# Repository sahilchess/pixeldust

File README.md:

# Pixeldust 🌟

Pixeldust is a new (in development) YSWS @ Hack Club! Create your own PCB design using KiCad, write the firmware for it in Wokwi, then receive your PCBs in the mail!

The website is still under development (guides etc. have been created yet) But the home page of the site has been created

## What is Pixeldust?

This is a brand new (in development) YSWS where you design your own neopixel-based PCB trinket, and we'll ship it to you for free! Make sure to join #pixeldust in the slack so you dont miss out!!

### You ship...

- A PCB design for the board
- Working firmware to control the neopixels

### We ship...

- 1 fully assembled PCB
   - This will include your XIAO RP2040 as well as the neopixels

- 2 unassembled PCBs

## Requirements

- Your firmware must be working!!! We won't approve any without.
- It must be more complex than just a simple blinking LED
- Your PCB cannot exceed 100cm^2
- Your PCB must only use 2 layers

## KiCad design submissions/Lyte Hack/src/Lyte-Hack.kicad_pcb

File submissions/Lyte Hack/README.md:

---
name: "Reem Ahrabar"
slack_id: "U07TZLFLJFR"
github_handle: "@cloudTwelve"
tutorial: "https://pixeldust.hackclub.com/guidelines"
wokwi: "https://wokwi.com/projects/428996000515740673"
---

# Lyte Hack

Wokwi link: [https://wokwi.com/projects/428996000515740673](https://wokwi.com/projects/428996000515740673)

<!-- Uncomment the line below if you need a soldering iron -->
<!-- ⚠️ I would like to solder the pieces of the board myself, so I would need some solder (I have an iron, but lost my solder). Nevermind, disregard -->

### Description
This is my submission for Hack Club's Pixeldust YSWS, and it's for a light that goes beneath a water bottle to turn it into a lamp. It was inspired by a life hack I heard of when I was younger and loved watching life hack videos, which instructed the viewer to put their phone's flashlight beneath a bottle to turn it into a lamp. I thought it'd be great to make a PCB version of this (with, inshaAllah/God willing, a 3D printed case + model for this later) since I had the opportunity.

### Concept Images

### Features
- 2 modes:
  -  White
  -  Color
    - Red
    - Orange
    - Yellow
    - Green
    - Turquoise
    - Blue
    - Indigo
    - Purple
    - Cotton candy (interspersed pale blue/pink)

### A simplified BOM table
(pls include rough pricing of any extra components you're using)

| Comment           | Footprint                                      | Quantity | LCSC     | Cost   |
|-------------------|------------------------------------------------|----------|----------|--------|
| 100uF             | C_1206_3216Metric_Pad1.33x1.80mm_HandSolder    | 1        | C15008   | 0.0682$|
| 4.7nF             | C_0402_1005Metric_Pad0.74x0.62mm_HandSolder    | 3        | C1538    | 0.0011$|
| SK6812MINI        | LED_SK6812MINI_PLCC4_3.5x3.5mm_P1.75mm         | 10       |          |
| XIAO-RP2040-DIP   | XIAO-RP2040-DIP                                | 1        |          |
| B3S-1000          | SW_SPST_B3S-1000                               | 2        | C2733655 | 0.2327$ each for 5|

### Planning/Making
I started this when the event was already over, and I had been thinking of chilling with hw late at night using the lamp life hack, realizing it could be translated to a PCB + 3D printed design. Since I had already done Hackpad V2 (still waiting on a PR approval though) for the macropad, I had a small but encouraging history with PCBs. I was ready to try again and make something fun, so I tried speedrunning this.

#### The Schematic
This went quickly. Following the guide given on the pixeldust website, I breezed through. The only new thing was the concept of decoupling capacitors (I should really learn electrical engineering...). I had to change a footprint when filling out the README, since the button I initially used (B3S-1100) was out of stock.

#### The PCB
This was also simple, I just listened to YouTube lectures and podcasts while I positioned and routed the items. The routing is pretty sloppy, in the future I'd probably watch a video on cleaner routing + good practices before doing this. Nevertheless, Hackpad gave me a good base, and the only issue I had was having to come back when small schematic issues cropped up (eg. changing the footprint for the button) and re-route/reposition items.

#### The Firmware
I had high aspirations that were partially fulfilled. Initially, I wanted 3 modes, static white, static color, and animated color, but I ended up throwing out the animated mode because of time. Some struggles I faced were:
- Finding the button library. Wokwi used MicroPython, not CircuitPython. I'd never used either, but I initially used the button library from CircuitPython.
- Getting the neopixel library to work. Same issue as above.
- Button timing. Often, the button would register multiple times on one click, and to fix it, I disabled the interrupt function, delayed 0.75s, and then enabled it again.

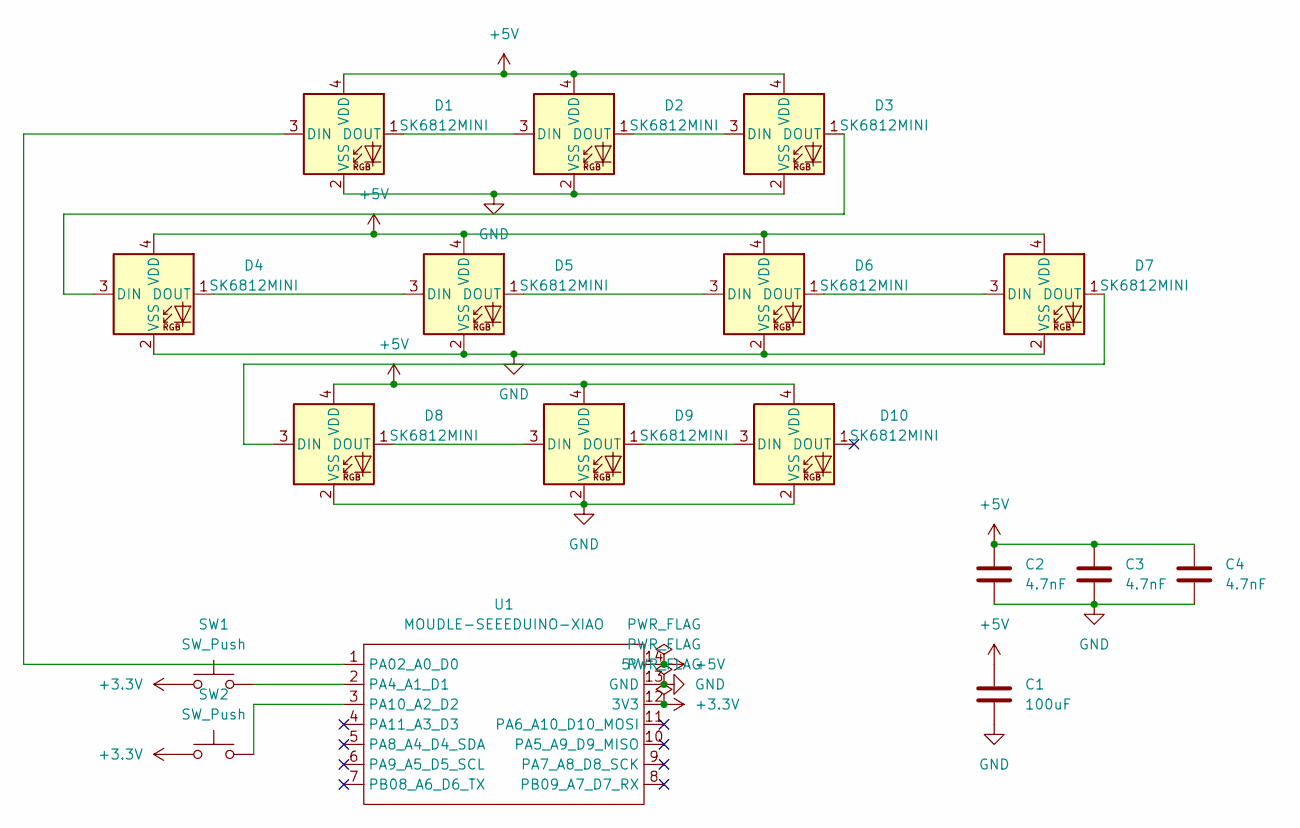
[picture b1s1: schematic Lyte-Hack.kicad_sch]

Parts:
C1: 100uF; C_1206_3216Metric_Pad1.33x1.80mm_HandSolder
C2, C3, C4: 4.7nF; C_0402_1005Metric_Pad0.74x0.62mm_HandSolder
D1, D2, D3, D4, D5, D6, D7, D8, D9, D10: SK6812MINI; LED_SK6812MINI_PLCC4_3.5x3.5mm_P1.75mm
SW1, SW2: SW_Push; SW_SPST_B3S-1000
U1: MOUDLE-SEEEDUINO-XIAO; MOUDLE14P-2.54-21X17.8MM

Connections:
+3.3V: SW1.1, SW2.1, U1.12 (3V3)
+5V: C1.1, C2.1, C3.1, C4.1, D1.4 (VDD), D2.4 (VDD), D3.4 (VDD), D4.4 (VDD), D5.4 (VDD), D6.4 (VDD), D7.4 (VDD), D8.4 (VDD), D9.4 (VDD), D10.4 (VDD), U1.14 (5V)
GND: C1.2, C2.2, C3.2, C4.2, D1.2 (VSS), D2.2 (VSS), D3.2 (VSS), D4.2 (VSS), D5.2 (VSS), D6.2 (VSS), D7.2 (VSS), D8.2 (VSS), D9.2 (VSS), D10.2 (VSS), U1.13 (GND)
unnamed: D1.3 (DIN), U1.1 (PA02_A0_D0)
unnamed: D1.1 (DOUT), D2.3 (DIN)
unnamed: D2.1 (DOUT), D3.3 (DIN)
unnamed: D3.1 (DOUT), D4.3 (DIN)
unnamed: D4.1 (DOUT), D5.3 (DIN)
unnamed: D5.1 (DOUT), D6.3 (DIN)
unnamed: D6.1 (DOUT), D7.3 (DIN)
unnamed: D7.1 (DOUT), D8.3 (DIN)
unnamed: D8.1 (DOUT), D9.3 (DIN)
unnamed: D9.1 (DOUT), D10.3 (DIN)
unnamed: SW1.2, U1.2 (PA4_A1_D1)
unnamed: SW2.2, U1.3 (PA10_A2_D2)

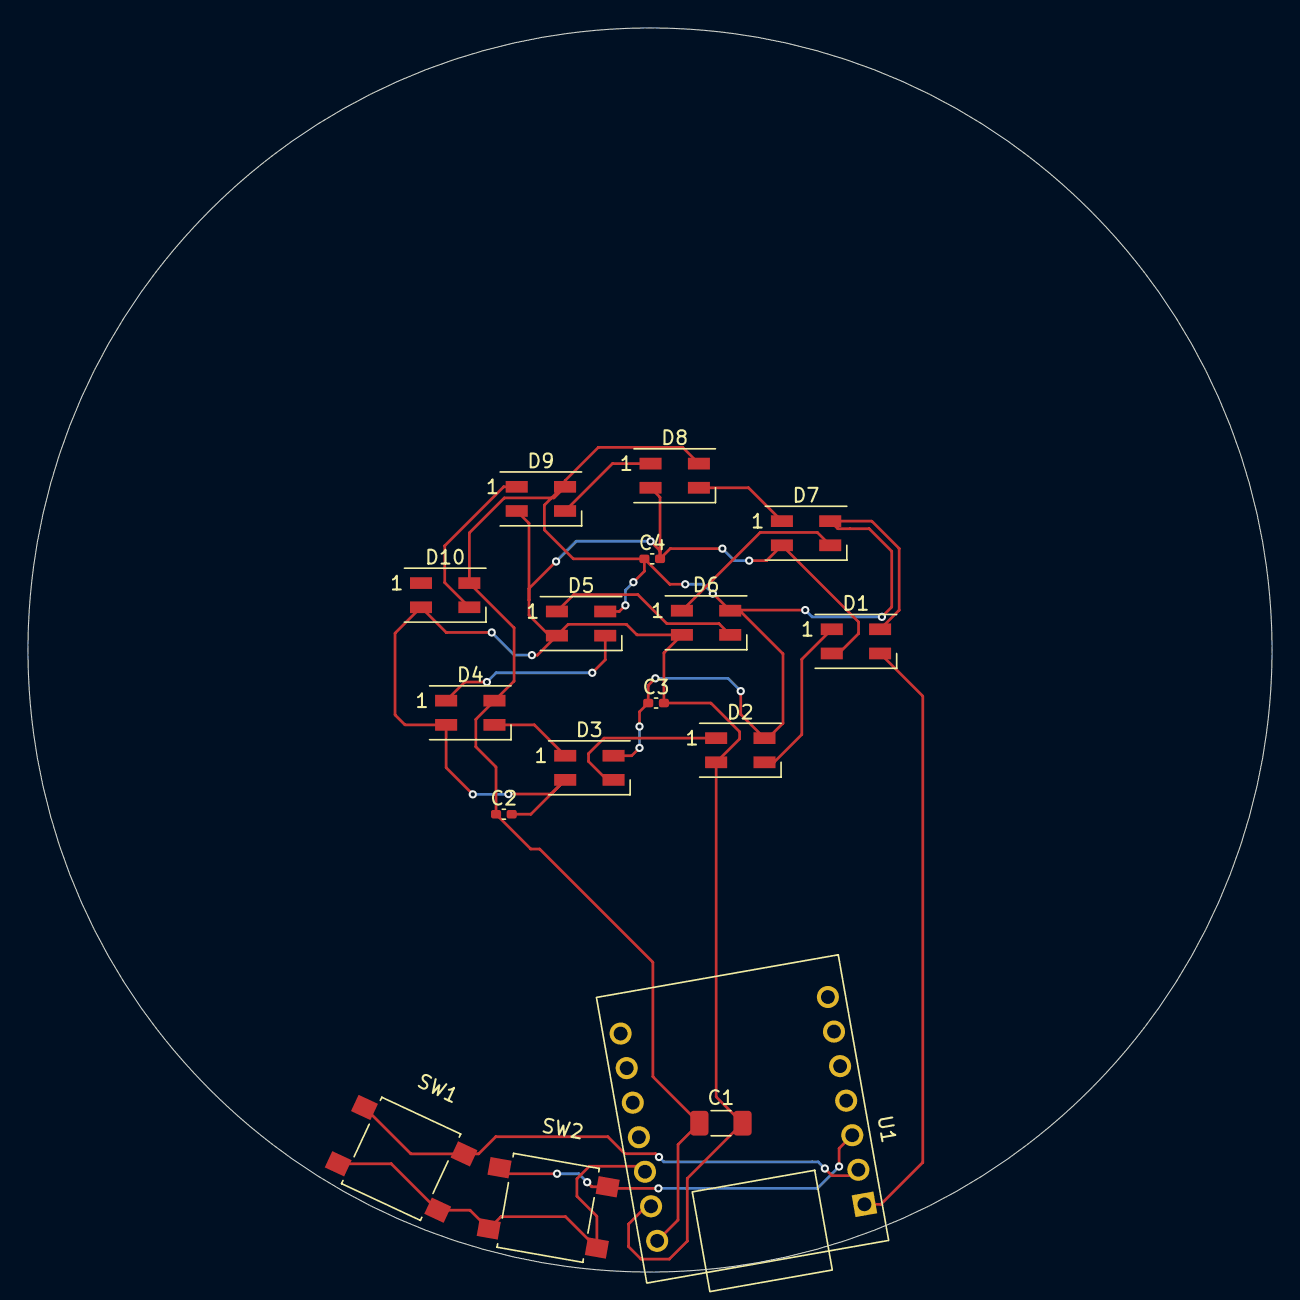
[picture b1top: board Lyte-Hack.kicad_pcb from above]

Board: 2 copper layers, 90.1 x 90.1 mm, 17 parts (0 on the bottom side), 15 nets.

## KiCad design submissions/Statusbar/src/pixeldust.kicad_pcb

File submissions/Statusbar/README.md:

---
name: "Elijah Spitzer"
slack_handle: "@Elijah Spitzer"
github_handle: "@elijahrs-gh"
tutorial: I read through Guidlines if that counts as one https://pixeldust.vercel.app/guidelines
wokwi: https://wokwi.com/projects/426786875779427329
---

# Statusbar

Wokwi link: [https://wokwi.com/projects/426786875779427329](https://wokwi.com/projects/426786875779427329)

My board is a statusbar / multi-functional appliance, it is primarily software based for control and is setup so it can easily show the progress you have on an application or be used to display other information.

A simplified BOM table ( detailed one is included in the repo ):
"SK6812","20",
"XIAO-RP2040-DIP","1",

When designing my PCB I had a few goals in mind:
* Useable, I want it to be stylish but something I will actually use.
* Multi-functinal, I needed it to be used for a variety of actions, such as a Statusbar or for LED displays for whatever purpose.
* Case, it should be able to fit in a case I can design.

I ended up designing this schematic, due to it being software based I didn't need it to have any extra controls, such as buttons:

I had issues with Kicad crashing a lot, it has a ton of memory leaks, but I was able to design and sketch the PCB in the shape I actually wanted:

Here is what the final result looked like!:

The next thing I had was software design and testing. I went through a bunch of libraries and found the adafruit neopixel which is what I decided to stick with.

I had a ton of issues with only one turning on, or none working and I spent hours debugging. I then redid how it was wired in Wokwi ( the simulator ) and it started working. It turns out because all the wires just merge together a few were off and it messed up the entire thing.

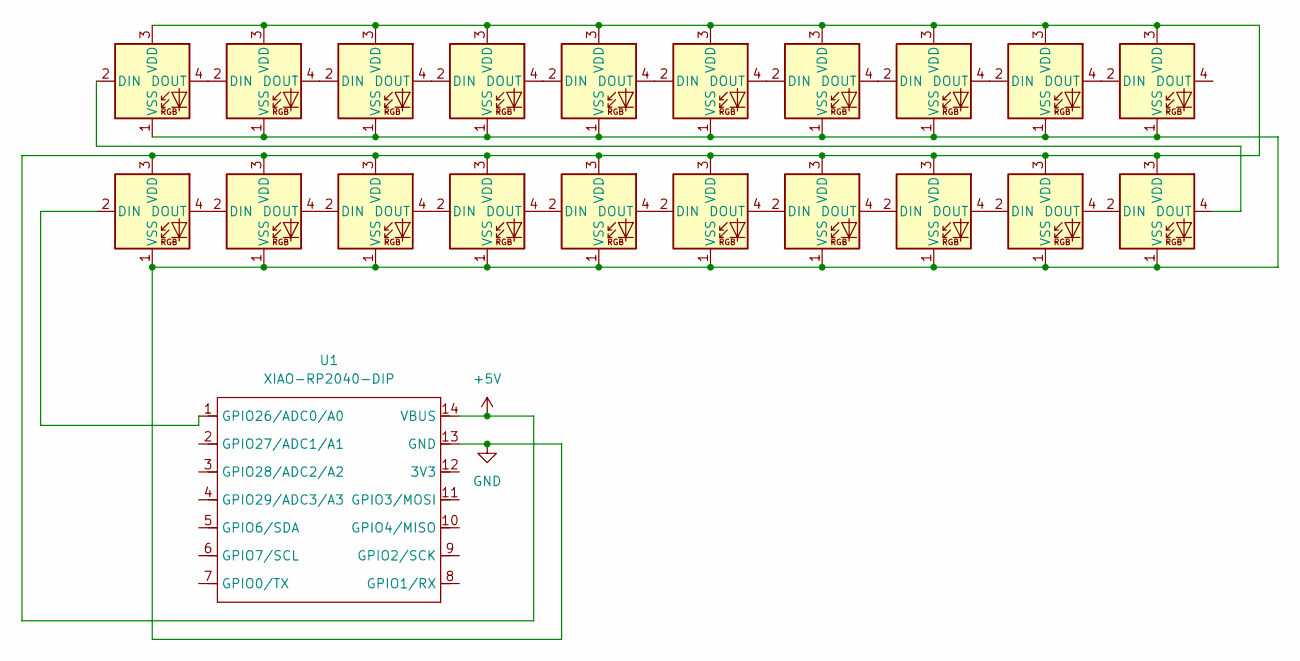
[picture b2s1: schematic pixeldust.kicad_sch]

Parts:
D1, D2, D3, D4, D5, D6, D7, D8, D9, D10, D11, D12, D13, D14, D15, D16, D17, D18, D19, D20: SK6812; LED_SK6812_PLCC4_5.0x5.0mm_P3.2mm
U1: XIAO-RP2040-DIP

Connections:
+5V: D1.3 (VDD), D2.3 (VDD), D3.3 (VDD), D4.3 (VDD), D5.3 (VDD), D6.3 (VDD), D7.3 (VDD), D8.3 (VDD), D9.3 (VDD), D10.3 (VDD), D11.3 (VDD), D12.3 (VDD), D13.3 (VDD), D14.3 (VDD), D15.3 (VDD), D16.3 (VDD), D17.3 (VDD), D18.3 (VDD), D19.3 (VDD), D20.3 (VDD), U1.14 (VBUS)
GND: D1.1 (VSS), D2.1 (VSS), D3.1 (VSS), D4.1 (VSS), D5.1 (VSS), D6.1 (VSS), D7.1 (VSS), D8.1 (VSS), D9.1 (VSS), D10.1 (VSS), D11.1 (VSS), D12.1 (VSS), D13.1 (VSS), D14.1 (VSS), D15.1 (VSS), D16.1 (VSS), D17.1 (VSS), D18.1 (VSS), D19.1 (VSS), D20.1 (VSS), U1.13 (GND)
unnamed: D1.2 (DIN), U1.1 (GPIO26/ADC0/A0)
unnamed: D1.4 (DOUT), D2.2 (DIN)
unnamed: D2.4 (DOUT), D3.2 (DIN)
unnamed: D3.4 (DOUT), D4.2 (DIN)
unnamed: D4.4 (DOUT), D5.2 (DIN)
unnamed: D5.4 (DOUT), D6.2 (DIN)
unnamed: D6.4 (DOUT), D7.2 (DIN)
unnamed: D7.4 (DOUT), D8.2 (DIN)
unnamed: D8.4 (DOUT), D9.2 (DIN)
unnamed: D9.4 (DOUT), D10.2 (DIN)
unnamed: D10.4 (DOUT), D11.2 (DIN)
unnamed: D11.4 (DOUT), D12.2 (DIN)
unnamed: D12.4 (DOUT), D13.2 (DIN)
unnamed: D13.4 (DOUT), D14.2 (DIN)
unnamed: D14.4 (DOUT), D15.2 (DIN)
unnamed: D15.4 (DOUT), D16.2 (DIN)
unnamed: D16.4 (DOUT), D17.2 (DIN)
unnamed: D17.4 (DOUT), D18.2 (DIN)
unnamed: D18.4 (DOUT), D19.2 (DIN)
unnamed: D19.4 (DOUT), D20.2 (DIN)

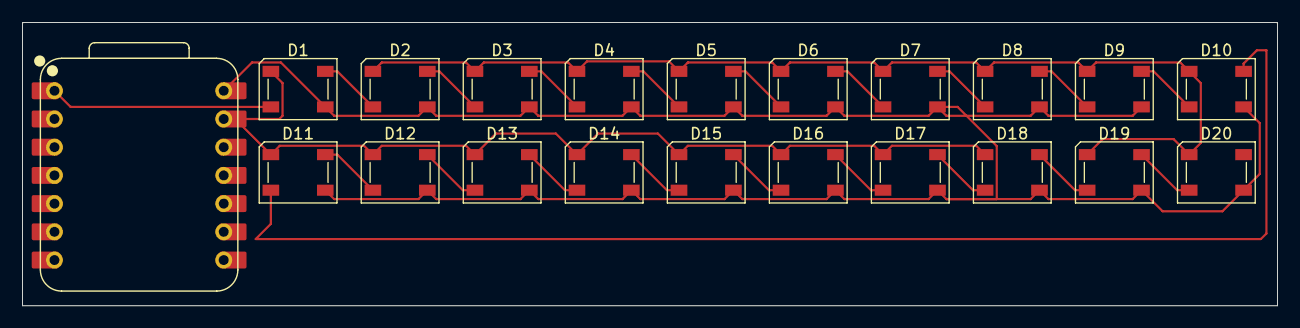
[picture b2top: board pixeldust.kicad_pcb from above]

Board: 2 copper layers, 113.0 x 25.5 mm, 21 parts (0 on the bottom side), 22 nets.

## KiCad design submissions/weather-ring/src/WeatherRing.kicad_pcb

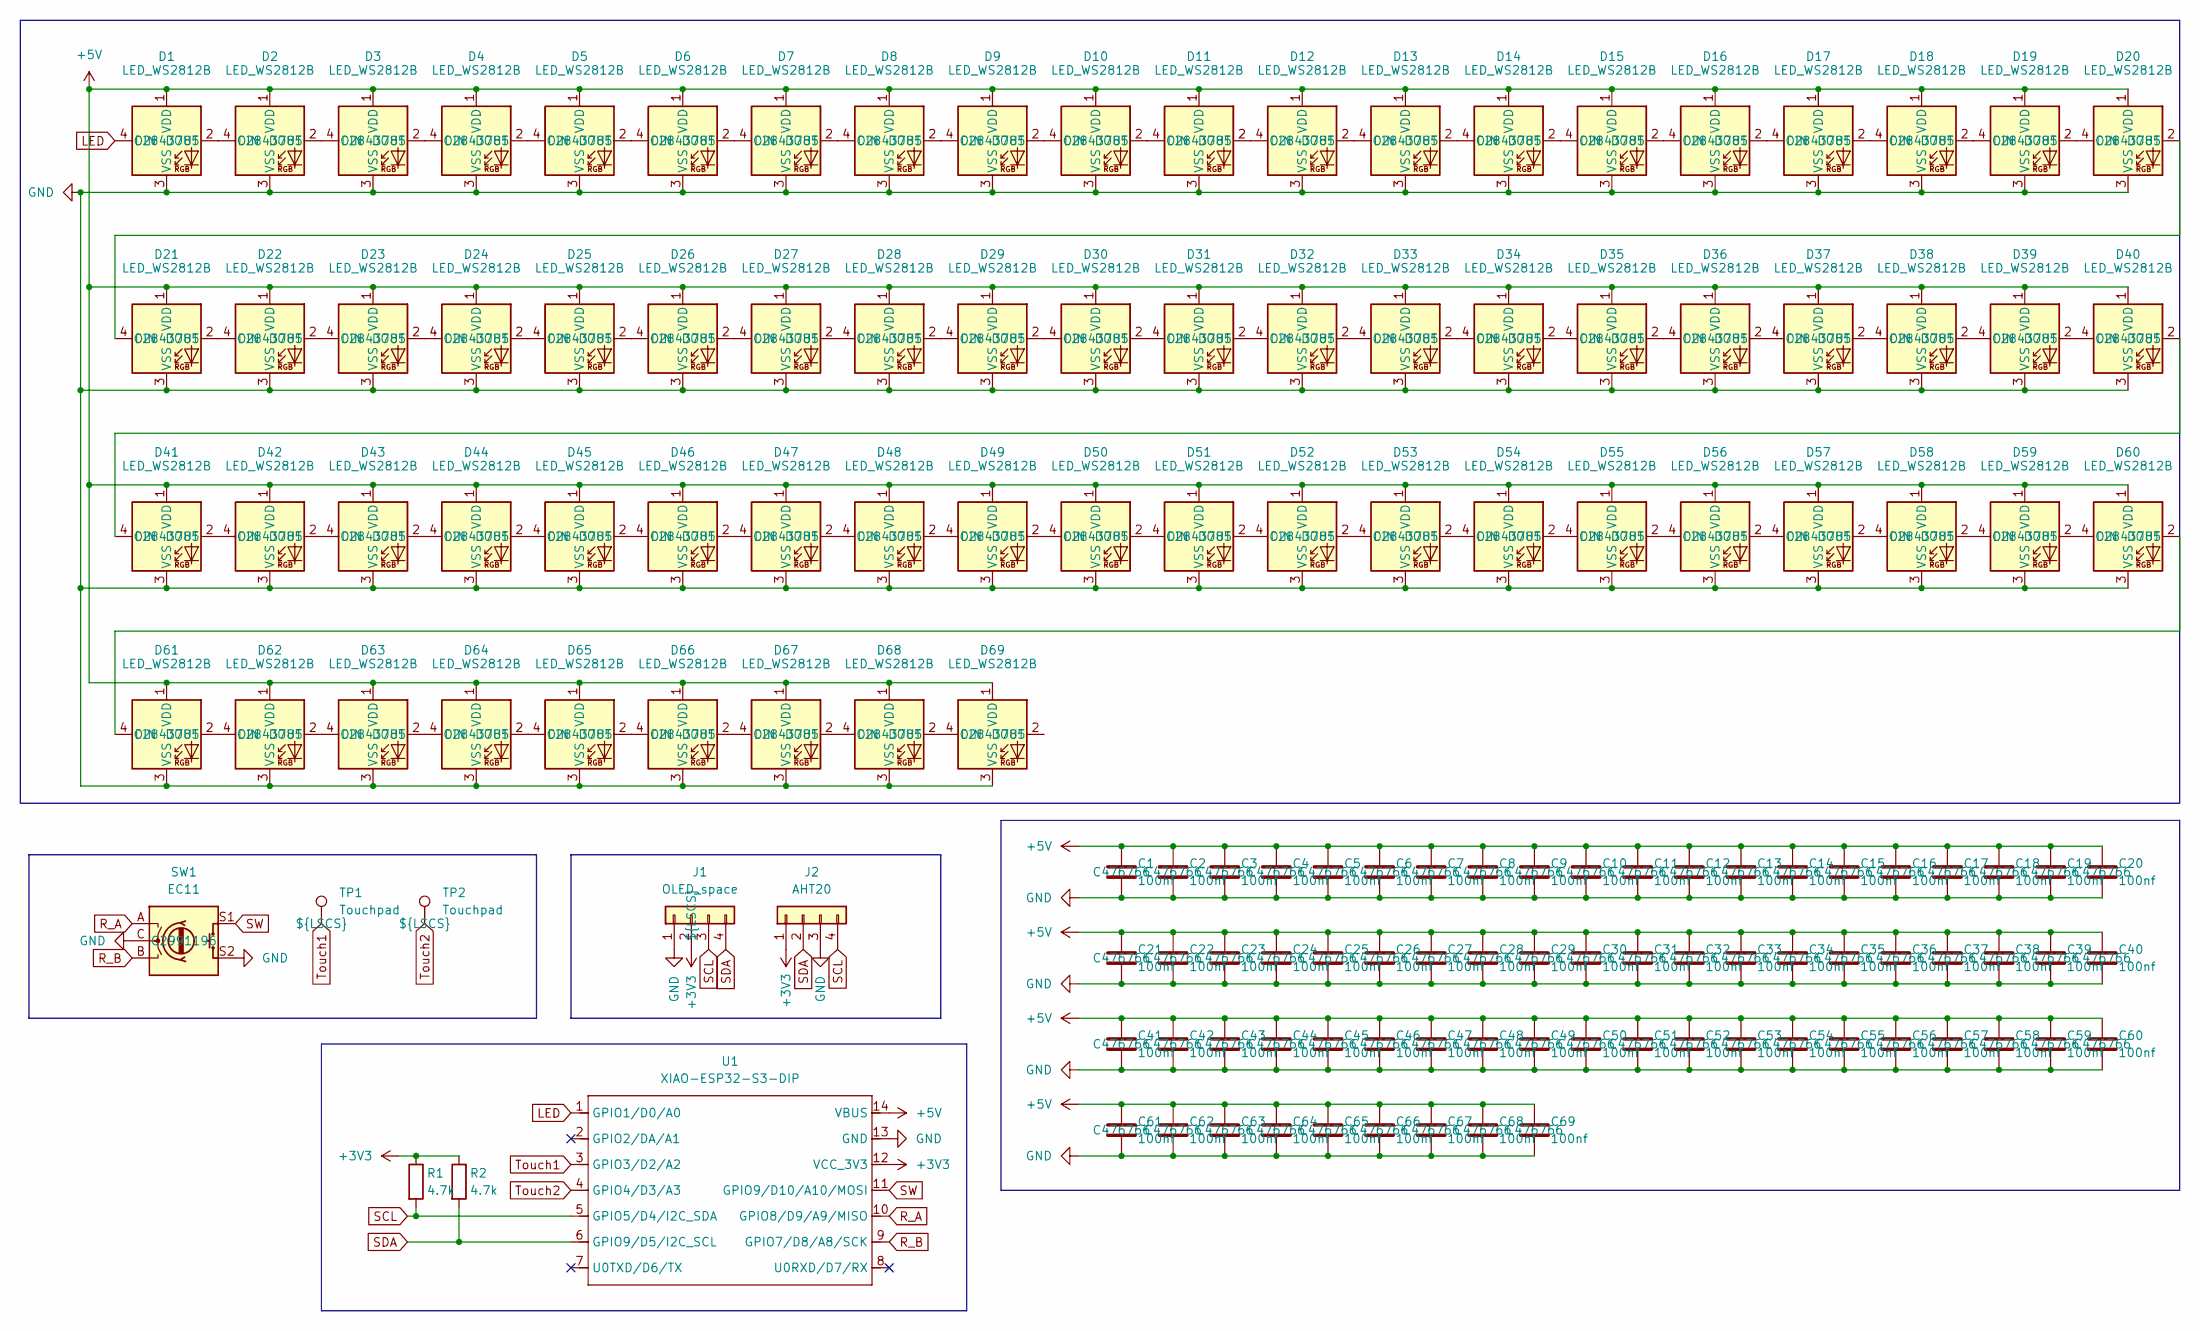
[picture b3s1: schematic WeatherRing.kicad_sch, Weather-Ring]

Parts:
C1, C2, C3, C4, C5, C6, C7, C8, C9, C10, C11, C12, C13, C14, C15, C16, C17, C18, C19, C20, C21, C22, C23, C24, C25, C26, C27, C28, C29, C30, C31, C32, C33, C34, C35, C36, C37, C38, C39, C40, C41, C42, C43, C44, C45, C46, C47, C48, C49, C50, C51, C52, C53, C54, C55, C56, C57, C58, C59, C60, C61, C62, C63, C64, C65, C66, C67, C68, C69: 100nf; C_0805_2012Metric_HandSolder_EDITED
D1, D2, D3, D4, D5, D6, D7, D8, D9, D10, D11, D12, D13, D14, D15, D16, D17, D18, D19, D20, D21, D22, D23, D24, D25, D26, D27, D28, D29, D30, D31, D32, D33, D34, D35, D36, D37, D38, D39, D40, D41, D42, D43, D44, D45, D46, D47, D48, D49, D50, D51, D52, D53, D54, D55, D56, D57, D58, D59, D60, D61, D62, D63, D64, D65, D66, D67, D68, D69: LED_WS2812B; LED_WS2812B_EDITED
J1: OLED_space; PinHeader_1x04_P2.54mm_Vertical
J2: AHT20; PinHeader_1x04_P2.54mm_Vertical
R1, R2: 4.7k; C_0805_2012Metric_HandSolder_EDITED
SW1: EC11; RotaryEncoder_EC11
TP1, TP2: Touchpad; TestPoint_Pad_D10.0mm
U1: XIAO-ESP32-S3-DIP; XIAO-ESP32S3-DIP

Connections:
+3V3: J1.2, J2.1, R1.1, R2.1, U1.12 (VCC_3V3)
+5V: C1.1, C2.1, C3.1, C4.1, C5.1, C6.1, C7.1, C8.1, C9.1, C10.1, C11.1, C12.1, C13.1, C14.1, C15.1, C16.1, C17.1, C18.1, C19.1, C20.1, C21.1, C22.1, C23.1, C24.1, C25.1, C26.1, C27.1, C28.1, C29.1, C30.1, C31.1, C32.1, C33.1, C34.1, C35.1, C36.1, C37.1, C38.1, C39.1, C40.1, C41.1, C42.1, C43.1, C44.1, C45.1, C46.1, C47.1, C48.1, C49.1, C50.1, C51.1, C52.1, C53.1, C54.1, C55.1, C56.1, C57.1, C58.1, C59.1, C60.1, C61.1, C62.1, C63.1, C64.1, C65.1, C66.1, C67.1, C68.1, C69.1, D1.1 (VDD), D2.1 (VDD), D3.1 (VDD), D4.1 (VDD), D5.1 (VDD), D6.1 (VDD), D7.1 (VDD), D8.1 (VDD), D9.1 (VDD), D10.1 (VDD), D11.1 (VDD), D12.1 (VDD), D13.1 (VDD), D14.1 (VDD), D15.1 (VDD), D16.1 (VDD), D17.1 (VDD), D18.1 (VDD), D19.1 (VDD), D20.1 (VDD), D21.1 (VDD), D22.1 (VDD), D23.1 (VDD), D24.1 (VDD), D25.1 (VDD), D26.1 (VDD), D27.1 (VDD), D28.1 (VDD), D29.1 (VDD), D30.1 (VDD), D31.1 (VDD), D32.1 (VDD), D33.1 (VDD), D34.1 (VDD), D35.1 (VDD), D36.1 (VDD), D37.1 (VDD), D38.1 (VDD), D39.1 (VDD), D40.1 (VDD), D41.1 (VDD), D42.1 (VDD), D43.1 (VDD), D44.1 (VDD), D45.1 (VDD), D46.1 (VDD), D47.1 (VDD), D48.1 (VDD), D49.1 (VDD), D50.1 (VDD), D51.1 (VDD), D52.1 (VDD), D53.1 (VDD), D54.1 (VDD), D55.1 (VDD), D56.1 (VDD), D57.1 (VDD), D58.1 (VDD), D59.1 (VDD), D60.1 (VDD), D61.1 (VDD), D62.1 (VDD), D63.1 (VDD), D64.1 (VDD), D65.1 (VDD), D66.1 (VDD), D67.1 (VDD), D68.1 (VDD), D69.1 (VDD), U1.14 (VBUS)
GND: C1.2, C2.2, C3.2, C4.2, C5.2, C6.2, C7.2, C8.2, C9.2, C10.2, C11.2, C12.2, C13.2, C14.2, C15.2, C16.2, C17.2, C18.2, C19.2, C20.2, C21.2, C22.2, C23.2, C24.2, C25.2, C26.2, C27.2, C28.2, C29.2, C30.2, C31.2, C32.2, C33.2, C34.2, C35.2, C36.2, C37.2, C38.2, C39.2, C40.2, C41.2, C42.2, C43.2, C44.2, C45.2, C46.2, C47.2, C48.2, C49.2, C50.2, C51.2, C52.2, C53.2, C54.2, C55.2, C56.2, C57.2, C58.2, C59.2, C60.2, C61.2, C62.2, C63.2, C64.2, C65.2, C66.2, C67.2, C68.2, C69.2, D1.3 (VSS), D2.3 (VSS), D3.3 (VSS), D4.3 (VSS), D5.3 (VSS), D6.3 (VSS), D7.3 (VSS), D8.3 (VSS), D9.3 (VSS), D10.3 (VSS), D11.3 (VSS), D12.3 (VSS), D13.3 (VSS), D14.3 (VSS), D15.3 (VSS), D16.3 (VSS), D17.3 (VSS), D18.3 (VSS), D19.3 (VSS), D20.3 (VSS), D21.3 (VSS), D22.3 (VSS), D23.3 (VSS), D24.3 (VSS), D25.3 (VSS), D26.3 (VSS), D27.3 (VSS), D28.3 (VSS), D29.3 (VSS), D30.3 (VSS), D31.3 (VSS), D32.3 (VSS), D33.3 (VSS), D34.3 (VSS), D35.3 (VSS), D36.3 (VSS), D37.3 (VSS), D38.3 (VSS), D39.3 (VSS), D40.3 (VSS), D41.3 (VSS), D42.3 (VSS), D43.3 (VSS), D44.3 (VSS), D45.3 (VSS), D46.3 (VSS), D47.3 (VSS), D48.3 (VSS), D49.3 (VSS), D50.3 (VSS), D51.3 (VSS), D52.3 (VSS), D53.3 (VSS), D54.3 (VSS), D55.3 (VSS), D56.3 (VSS), D57.3 (VSS), D58.3 (VSS), D59.3 (VSS), D60.3 (VSS), D61.3 (VSS), D62.3 (VSS), D63.3 (VSS), D64.3 (VSS), D65.3 (VSS), D66.3 (VSS), D67.3 (VSS), D68.3 (VSS), D69.3 (VSS), J1.1, J2.3, SW1.C, SW1.S2, U1.13 (GND)
LED: D1.4 (DIN), U1.1 (GPIO1/D0/A0)
unnamed: D1.2 (DOUT), D2.4 (DIN)
unnamed: D2.2 (DOUT), D3.4 (DIN)
unnamed: D3.2 (DOUT), D4.4 (DIN)
unnamed: D4.2 (DOUT), D5.4 (DIN)
unnamed: D5.2 (DOUT), D6.4 (DIN)
unnamed: D6.2 (DOUT), D7.4 (DIN)
unnamed: D7.2 (DOUT), D8.4 (DIN)
unnamed: D8.2 (DOUT), D9.4 (DIN)
unnamed: D9.2 (DOUT), D10.4 (DIN)
unnamed: D10.2 (DOUT), D11.4 (DIN)
unnamed: D11.2 (DOUT), D12.4 (DIN)
unnamed: D12.2 (DOUT), D13.4 (DIN)
unnamed: D13.2 (DOUT), D14.4 (DIN)
unnamed: D14.2 (DOUT), D15.4 (DIN)
unnamed: D15.2 (DOUT), D16.4 (DIN)
unnamed: D16.2 (DOUT), D17.4 (DIN)
unnamed: D17.2 (DOUT), D18.4 (DIN)
unnamed: D18.2 (DOUT), D19.4 (DIN)
unnamed: D19.2 (DOUT), D20.4 (DIN)
unnamed: D20.2 (DOUT), D21.4 (DIN)
unnamed: D21.2 (DOUT), D22.4 (DIN)
unnamed: D22.2 (DOUT), D23.4 (DIN)
unnamed: D23.2 (DOUT), D24.4 (DIN)
unnamed: D24.2 (DOUT), D25.4 (DIN)
unnamed: D25.2 (DOUT), D26.4 (DIN)
unnamed: D26.2 (DOUT), D27.4 (DIN)
unnamed: D27.2 (DOUT), D28.4 (DIN)
unnamed: D28.2 (DOUT), D29.4 (DIN)
unnamed: D29.2 (DOUT), D30.4 (DIN)
unnamed: D30.2 (DOUT), D31.4 (DIN)
unnamed: D31.2 (DOUT), D32.4 (DIN)
unnamed: D32.2 (DOUT), D33.4 (DIN)
unnamed: D33.2 (DOUT), D34.4 (DIN)
unnamed: D34.2 (DOUT), D35.4 (DIN)
unnamed: D35.2 (DOUT), D36.4 (DIN)
unnamed: D36.2 (DOUT), D37.4 (DIN)
unnamed: D37.2 (DOUT), D38.4 (DIN)
unnamed: D38.2 (DOUT), D39.4 (DIN)
unnamed: D39.2 (DOUT), D40.4 (DIN)
unnamed: D40.2 (DOUT), D41.4 (DIN)
unnamed: D41.2 (DOUT), D42.4 (DIN)
unnamed: D42.2 (DOUT), D43.4 (DIN)
unnamed: D43.2 (DOUT), D44.4 (DIN)
unnamed: D44.2 (DOUT), D45.4 (DIN)
unnamed: D45.2 (DOUT), D46.4 (DIN)
unnamed: D46.2 (DOUT), D47.4 (DIN)
unnamed: D47.2 (DOUT), D48.4 (DIN)
unnamed: D48.2 (DOUT), D49.4 (DIN)
unnamed: D49.2 (DOUT), D50.4 (DIN)
unnamed: D50.2 (DOUT), D51.4 (DIN)
unnamed: D51.2 (DOUT), D52.4 (DIN)
unnamed: D52.2 (DOUT), D53.4 (DIN)
unnamed: D53.2 (DOUT), D54.4 (DIN)
unnamed: D54.2 (DOUT), D55.4 (DIN)
unnamed: D55.2 (DOUT), D56.4 (DIN)
unnamed: D56.2 (DOUT), D57.4 (DIN)
unnamed: D57.2 (DOUT), D58.4 (DIN)
unnamed: D58.2 (DOUT), D59.4 (DIN)
unnamed: D59.2 (DOUT), D60.4 (DIN)
unnamed: D60.2 (DOUT), D61.4 (DIN)
unnamed: D61.2 (DOUT), D62.4 (DIN)
unnamed: D62.2 (DOUT), D63.4 (DIN)
unnamed: D63.2 (DOUT), D64.4 (DIN)
unnamed: D64.2 (DOUT), D65.4 (DIN)
unnamed: D65.2 (DOUT), D66.4 (DIN)
unnamed: D66.2 (DOUT), D67.4 (DIN)
unnamed: D67.2 (DOUT), D68.4 (DIN)
unnamed: D68.2 (DOUT), D69.4 (DIN)
R_A: SW1.A, U1.10 (GPIO8/D9/A9/MISO)
R_B: SW1.B, U1.9 (GPIO7/D8/A8/SCK)
SCL: J1.3, J2.4, R1.2, U1.5 (GPIO5/D4/I2C_SDA)
SDA: J1.4, J2.2, R2.2, U1.6 (GPIO9/D5/I2C_SCL)
SW: SW1.S1, U1.11 (GPIO9/D10/A10/MOSI)
Touch1: TP1.1, U1.3 (GPIO3/D2/A2)
Touch2: TP2.1, U1.4 (GPIO4/D3/A3)

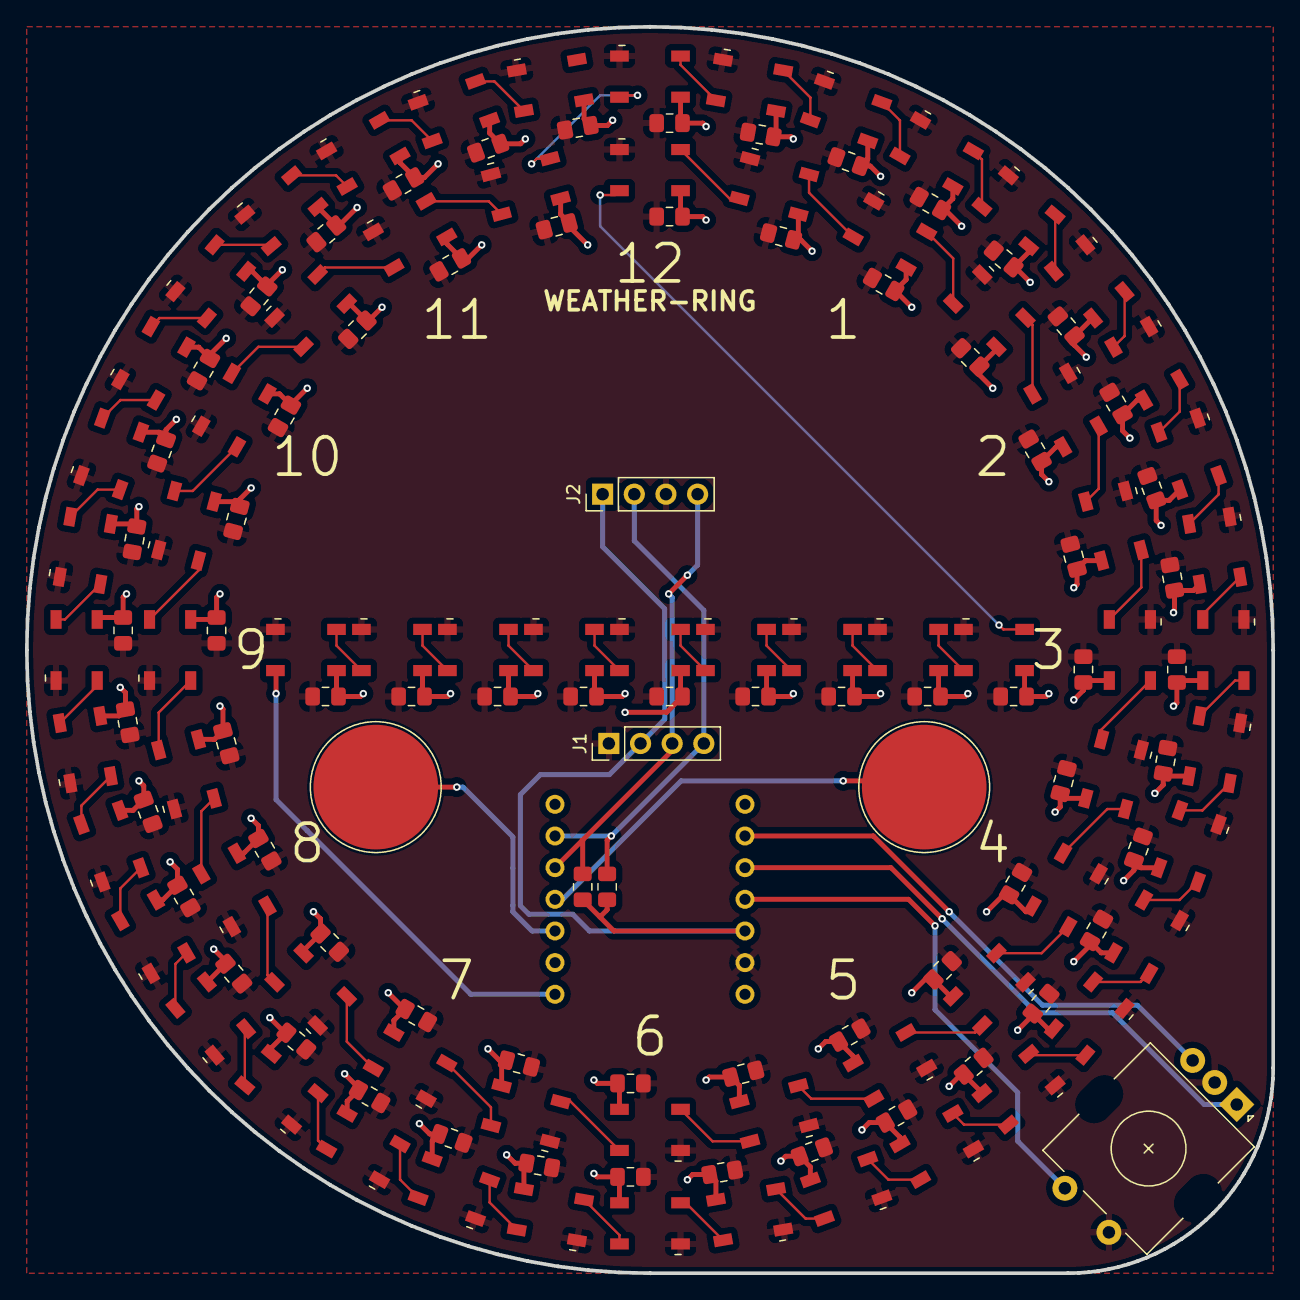
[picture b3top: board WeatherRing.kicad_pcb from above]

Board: 2 copper layers, 100.0 x 100.0 mm, 146 parts (1 on the bottom side), 79 nets.

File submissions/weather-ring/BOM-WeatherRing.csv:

"Value","Footprint","Qty","LSCS"
"AHT20","Connector_PinHeader_2.54mm:PinHeader_1x04_P2.54mm_Vertical","1",""
"EC11","Keebio-Parts.pretty-master:RotaryEncoder_EC11","1","C2991196"
"XIAO-ESP32-S3-DIP","Seeed Studio XIAO Series Library:XIAO-ESP32S3-DIP","1",""
"100nf","MyLibrary:C_0805_2012Metric_HandSolder_EDITED","69","C476766"
"LED_WS2812B","ScottoKeebs_Components:LED_WS2812B_EDITED","69","C2843785"
"4.7k","MyLibrary:C_0805_2012Metric_HandSolder_EDITED","2","C473295"

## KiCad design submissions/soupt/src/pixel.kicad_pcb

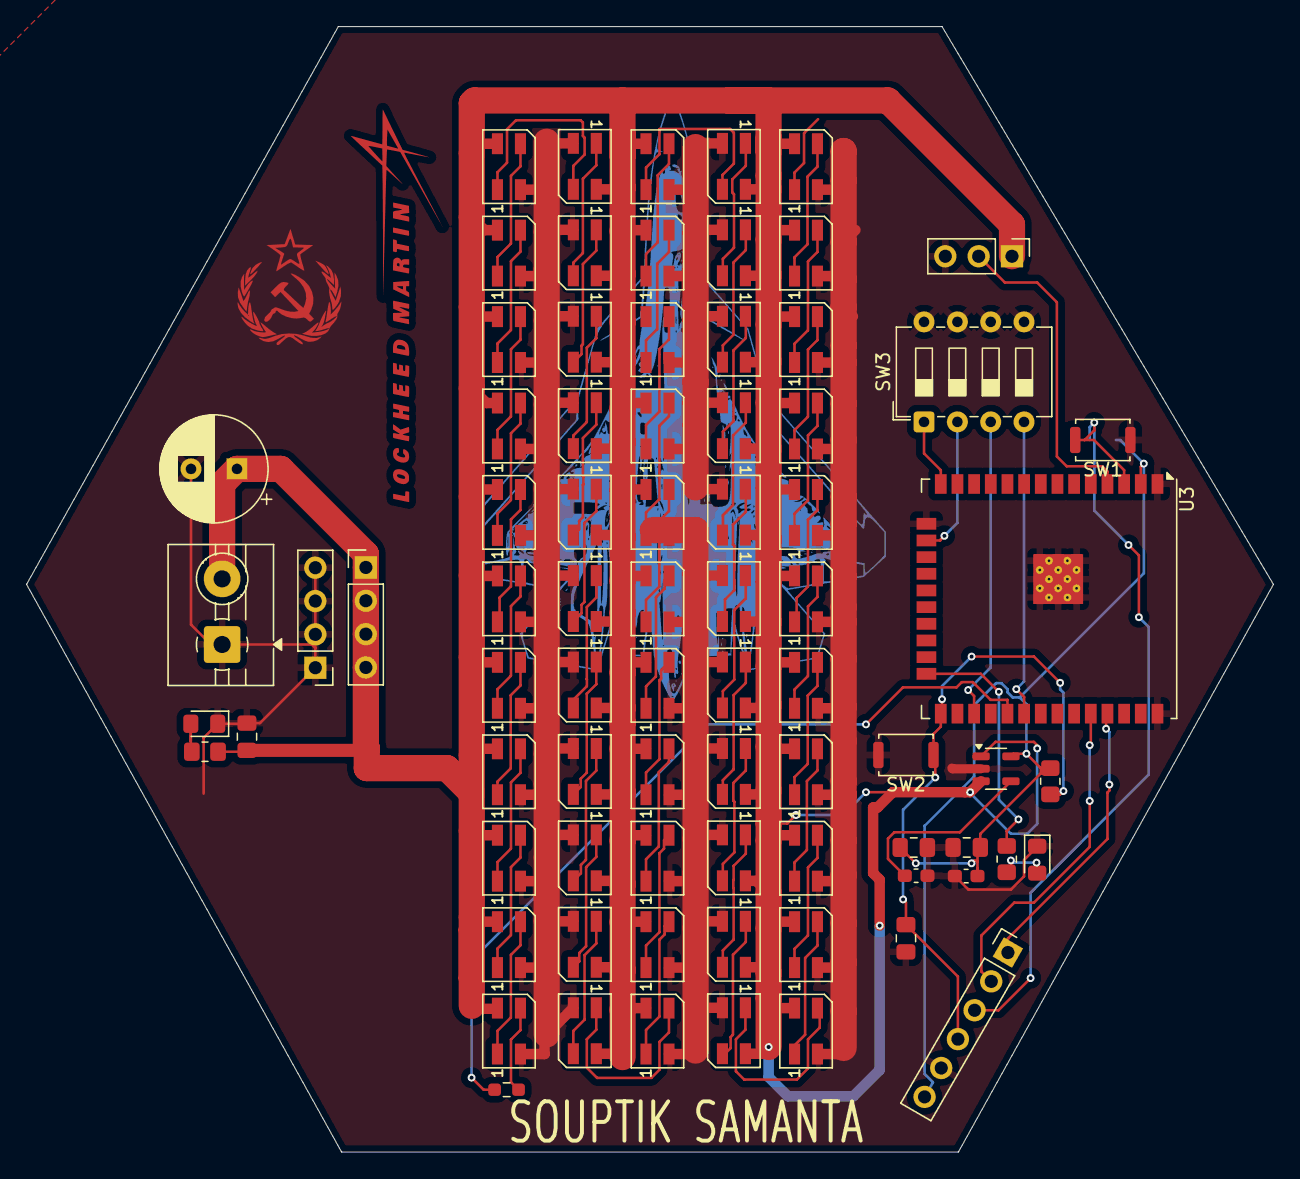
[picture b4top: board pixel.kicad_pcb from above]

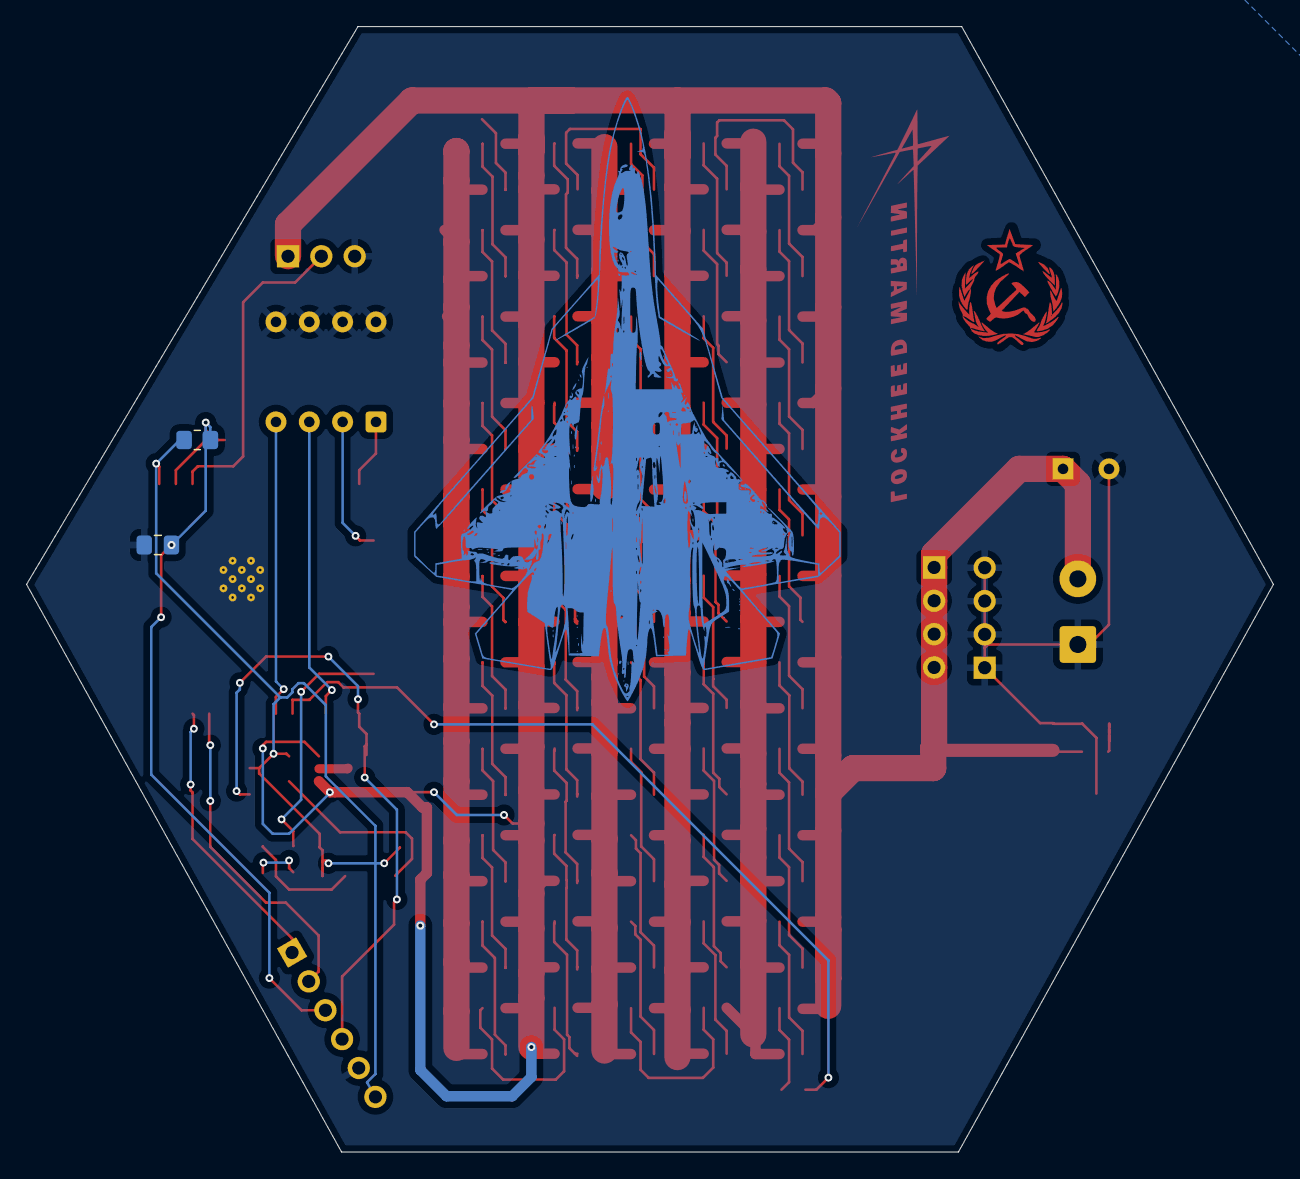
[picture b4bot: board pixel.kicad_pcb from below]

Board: 2 copper layers, 95.0 x 85.8 mm, 80 parts (2 on the bottom side), 72 nets.

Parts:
C1, C6: 0.1uF; C_0805_2012Metric_Pad1.18x1.45mm_HandSolder
C2: 0.1uf; C_0805_2012Metric_Pad1.18x1.45mm_HandSolder
C3: 22uf; C_0805_2012Metric_Pad1.18x1.45mm_HandSolder
C4: 22uF; C_0805_2012Metric_Pad1.18x1.45mm_HandSolder
C5: 2.2uf; C_0603_1608Metric_Pad1.08x0.95mm_HandSolder
C7: C_Polarized_Small; CP_Radial_D8.0mm_P3.50mm
C8: 470pf; C_0603_1608Metric_Pad1.08x0.95mm_HandSolder
D1, D2, D3, D4, D5, D6, D7, D8, D9, D10, D11, D12, D13, D14, D15, D16, D17, D18, D19, D20, D21, D22, D23, D24, D25, D26, D27, D28, D29, D30, D31, D32, D33, D34, D35, D36, D37, D38, D39, D40, D41, D42, D43, D44, D45, D46, D47, D48, D49, D50, D51, D52, D53, D54, D55: SK6812MINI; LED_SK6812MINI_PLCC4_3.5x3.5mm_P1.75mm
D121: Transmission Good; LED_0805_2012Metric_Pad1.15x1.40mm_HandSolder
D122: LED; LED_0805_2012Metric_Pad1.15x1.40mm_HandSolder
J1: Conn_01x03_Pin; PinHeader_1x03_P2.54mm_Vertical
J2, J4: Conn_01x04_Pin; PinHeader_1x04_P2.54mm_Vertical
J3: Conn_01x06_Pin; PinHeader_1x06_P2.54mm_Vertical
J8: Conn_01x02_Socket; TerminalBlock_MaiXu_MX126-5.0-02P_1x02_P5.00mm
R1: 330; R_0603_1608Metric_Pad0.98x0.95mm_HandSolder
R2: 330R; R_0805_2012Metric_Pad1.20x1.40mm_HandSolder
R3: 10k; R_0805_2012Metric_Pad1.20x1.40mm_HandSolder
R4: 10K; R_0805_2012Metric_Pad1.20x1.40mm_HandSolder
R5: 2K; R_0805_2012Metric_Pad1.20x1.40mm_HandSolder
SW1: RESET; SW_Push_SPST_NO_Alps_SKRK
SW2: BOOT; SW_Push_SPST_NO_Alps_SKRK
SW3: SW_DIP_x04; SW_DIP_SPSTx04_Slide_6.7x11.72mm_W7.62mm_P2.54mm_LowProfile
U2: MIC5219-3.3YM5; SOT-23-5
U3: ESP32-WROOM-32U

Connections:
+3V3: C2.2, C3.2, C5.2, J3.6, R3.2, R4.2, U2.5 (OUT), U3.2 (VDD)
+5V: C4.1, C7.1, D1.4 (VDD), D2.4 (VDD), D3.4 (VDD), D4.4 (VDD), D5.4 (VDD), D6.4 (VDD), D7.4 (VDD), D8.4 (VDD), D9.4 (VDD), D10.4 (VDD), D11.4 (VDD), D12.4 (VDD), D13.4 (VDD), D14.4 (VDD), D15.4 (VDD), D16.4 (VDD), D17.4 (VDD), D18.4 (VDD), D19.4 (VDD), D20.4 (VDD), D21.4 (VDD), D22.4 (VDD), D23.4 (VDD), D24.4 (VDD), D25.4 (VDD), D26.4 (VDD), D27.4 (VDD), D28.4 (VDD), D29.4 (VDD), D30.4 (VDD), D31.4 (VDD), D32.4 (VDD), D33.4 (VDD), D34.4 (VDD), D35.4 (VDD), D36.4 (VDD), D37.4 (VDD), D38.4 (VDD), D39.4 (VDD), D40.4 (VDD), D41.4 (VDD), D42.4 (VDD), D43.4 (VDD), D44.4 (VDD), D45.4 (VDD), D46.4 (VDD), D47.4 (VDD), D48.4 (VDD), D49.4 (VDD), D50.4 (VDD), D51.4 (VDD), D52.4 (VDD), D53.4 (VDD), D54.4 (VDD), D55.4 (VDD), J1.1, J4.1, J4.2, J4.3, J4.4, J8.2, R5.2, U2.1 (IN), U2.3 (EN)
DIN: D1.3 (DIN), R1.1
EN: C1.1, J3.3, R3.1, SW1.2, U3.3 (EN)
GND: C1.2, C2.1, C3.1, C4.2, C5.1, C6.2, C7.2, C8.2, D1.2 (VSS), D2.2 (VSS), D3.2 (VSS), D4.2 (VSS), D5.2 (VSS), D6.2 (VSS), D7.2 (VSS), D8.2 (VSS), D9.2 (VSS), D10.2 (VSS), D11.2 (VSS), D12.2 (VSS), D13.2 (VSS), D14.2 (VSS), D15.2 (VSS), D16.2 (VSS), D17.2 (VSS), D18.2 (VSS), D19.2 (VSS), D20.2 (VSS), D21.2 (VSS), D22.2 (VSS), D23.2 (VSS), D24.2 (VSS), D25.2 (VSS), D26.2 (VSS), D27.2 (VSS), D28.2 (VSS), D29.2 (VSS), D30.2 (VSS), D31.2 (VSS), D32.2 (VSS), D33.2 (VSS), D34.2 (VSS), D35.2 (VSS), D36.2 (VSS), D37.2 (VSS), D38.2 (VSS), D39.2 (VSS), D40.2 (VSS), D41.2 (VSS), D42.2 (VSS), D43.2 (VSS), D44.2 (VSS), D45.2 (VSS), D46.2 (VSS), D47.2 (VSS), D48.2 (VSS), D49.2 (VSS), D50.2 (VSS), D51.2 (VSS), D52.2 (VSS), D53.2 (VSS), D54.2 (VSS), D55.2 (VSS), D121.1 (K), D122.1 (K), J1.3, J2.1, J2.2, J2.3, J2.4, J3.5, J8.1, SW1.1, SW2.2, SW3.5, SW3.6, SW3.7, SW3.8, U2.2 (GND), U3.1 (GND), U3.15 (GND), U3.38 (GND), U3.39 (GND)
GPIO2: R2.1, U3.24 (IO2)
IO0: C6.1, J3.4, R4.1, SW2.1, U3.25 (IO0)
unnamed: D1.1 (DOUT), D2.3 (DIN)
unnamed: D2.1 (DOUT), D3.3 (DIN)
unnamed: D3.1 (DOUT), D4.3 (DIN)
unnamed: D4.1 (DOUT), D5.3 (DIN)
unnamed: D5.1 (DOUT), D6.3 (DIN)
unnamed: D6.1 (DOUT), D7.3 (DIN)
unnamed: D7.1 (DOUT), D8.3 (DIN)
unnamed: D8.1 (DOUT), D9.3 (DIN)
unnamed: D9.1 (DOUT), D10.3 (DIN)
unnamed: D10.1 (DOUT), D11.3 (DIN)
unnamed: D11.1 (DOUT), D12.3 (DIN)
unnamed: D12.1 (DOUT), D13.3 (DIN)
unnamed: D13.1 (DOUT), D14.3 (DIN)
unnamed: D14.1 (DOUT), D15.3 (DIN)
unnamed: D15.1 (DOUT), D16.3 (DIN)
unnamed: D16.1 (DOUT), D17.3 (DIN)
unnamed: D17.1 (DOUT), D18.3 (DIN)
unnamed: D18.1 (DOUT), D19.3 (DIN)
unnamed: D19.1 (DOUT), D20.3 (DIN)
unnamed: D20.1 (DOUT), D21.3 (DIN)
unnamed: D21.1 (DOUT), D22.3 (DIN)
unnamed: D22.1 (DOUT), D23.3 (DIN)
unnamed: D23.1 (DOUT), D24.3 (DIN)
unnamed: D24.1 (DOUT), D25.3 (DIN)
unnamed: D25.1 (DOUT), D26.3 (DIN)
unnamed: D26.1 (DOUT), D27.3 (DIN)
unnamed: D27.1 (DOUT), D28.3 (DIN)
unnamed: D28.1 (DOUT), D29.3 (DIN)
unnamed: D29.1 (DOUT), D30.3 (DIN)
unnamed: D30.1 (DOUT), D31.3 (DIN)
unnamed: D31.1 (DOUT), D32.3 (DIN)
unnamed: D32.1 (DOUT), D33.3 (DIN)
unnamed: D33.1 (DOUT), D34.3 (DIN)
unnamed: D34.1 (DOUT), D35.3 (DIN)
unnamed: D35.1 (DOUT), D36.3 (DIN)
unnamed: D36.1 (DOUT), D37.3 (DIN)
unnamed: D37.1 (DOUT), D38.3 (DIN)
unnamed: D38.1 (DOUT), D39.3 (DIN)
unnamed: D39.1 (DOUT), D40.3 (DIN)
unnamed: D40.1 (DOUT), D41.3 (DIN)
unnamed: D41.1 (DOUT), D42.3 (DIN)
unnamed: D42.1 (DOUT), D43.3 (DIN)
unnamed: D43.1 (DOUT), D44.3 (DIN)
unnamed: D44.1 (DOUT), D45.3 (DIN)
unnamed: D45.1 (DOUT), D46.3 (DIN)
unnamed: D46.1 (DOUT), D47.3 (DIN)
unnamed: D47.1 (DOUT), D48.3 (DIN)
unnamed: D48.1 (DOUT), D49.3 (DIN)
unnamed: D49.1 (DOUT), D50.3 (DIN)
unnamed: D50.1 (DOUT), D51.3 (DIN)
unnamed: D51.1 (DOUT), D52.3 (DIN)
unnamed: D52.1 (DOUT), D53.3 (DIN)
unnamed: D53.1 (DOUT), D54.3 (DIN)
unnamed: D54.1 (DOUT), D55.3 (DIN)
unnamed: D121.2 (A), R2.2
unnamed: D122.2 (A), R5.1
unnamed: J1.2, U3.4 (SENSOR_VP)
unnamed: C8.1, U2.4 (BP)
unnamed: R1.2, U3.29 (IO5)
unnamed: SW3.1, U3.14 (IO12)
unnamed: SW3.2, U3.16 (IO13)
unnamed: SW3.3, U3.27 (IO16)
unnamed: SW3.4, U3.30 (IO18)
RX: J3.2, U3.34 (RXD0/IO3)
TX: J3.1, U3.35 (TXD0/IO1)
